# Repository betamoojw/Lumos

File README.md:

# Lumos - Smart Lighting for Better Sleep
There are plenty of smart lighting systems out there that let you change light colors and dim with just your smartphone (or even your voice), but this Open Source lamp called Lumos is a smart lighting system that works to benefit your health.

Lumos mimics the natural light of the sun as it passes overhead each day, generating bright blue light in the morning and warmer amber light in the evening.
Decades of research from Harvard Medical School , NASA , and leading institutions around the world have revealed a great deal of information about how light impacts and regulates our health. They explain that blue light aids in the production of cortisol, which is important to give the human body energy in the morning, and red light aids in the production of sleep-inducing melatonin.
Almost 20% of the world's population is sleep deprived & possibly spends more than 8 hours a day under an unnatural light, which can throw off the body’s internal clock and prevent it from performing at optimum levels.

The Lumos smart lamp aims to change that by pairing with WiFi and uses Machine Learning to adjust the light to match your sleep schedule.

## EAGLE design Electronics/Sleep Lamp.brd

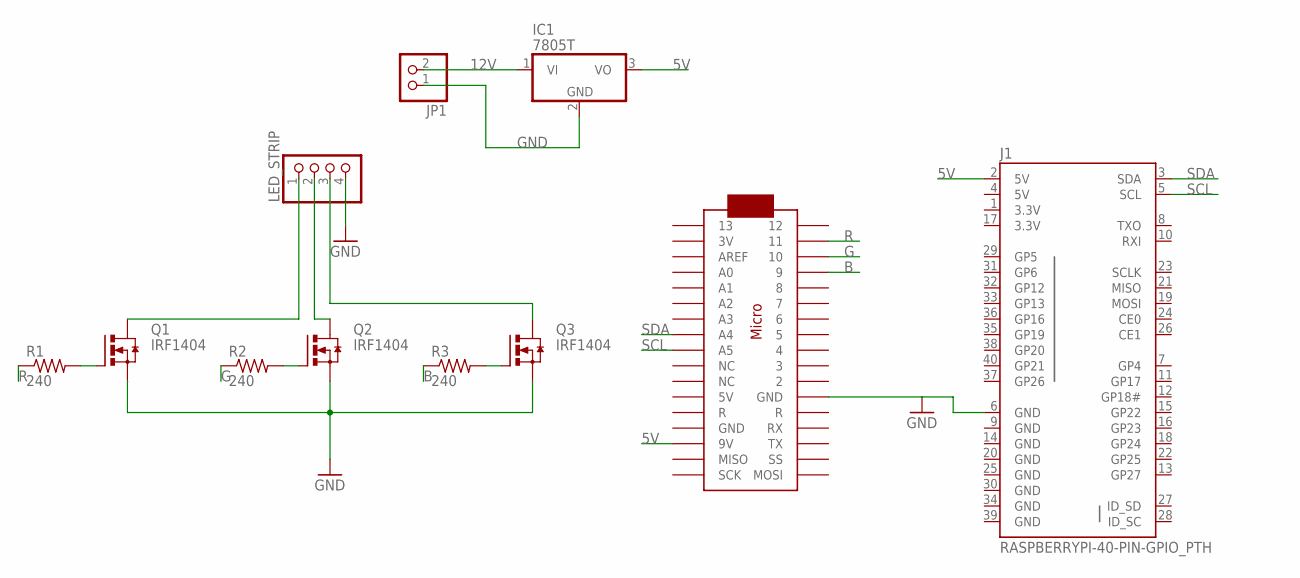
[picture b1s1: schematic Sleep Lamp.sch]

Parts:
IC1: 7805T; TO220H
J1: RASPBERRYPI-40-PIN-GPIO_PTH; 2X20_SHROUDED
JP1: PINHD-1X2; 1X02
LED_STRIP: PINHD-1X4; 1X04
Q1, Q2, Q3: IRF1404; TO220BH
R1, R2, R3: 240; 0204/7
U$1: ARDUINOMICRO

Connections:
3.3V: J1.1 (3.3V), J1.17 (3.3V)
5V: IC1.3 (VO), J1.2 (5V), J1.4 (5V), U$1.P$20 (9V)
12V: IC1.1 (VI), JP1.2
B: R3.1, U$1.P$4 (9)
G: R2.1, U$1.P$3 (10)
GND: IC1.2 (GND), J1.6 (GND), J1.9 (GND), J1.14 (GND), J1.20 (GND), J1.25 (GND), J1.30 (GND), J1.34 (GND), J1.39 (GND), JP1.1, LED_STRIP.4, Q1.S, Q2.S, Q3.S, U$1.P$21 (GND)
unnamed: LED_STRIP.2, Q2.D
unnamed: LED_STRIP.3, Q3.D
unnamed: LED_STRIP.1, Q1.D
unnamed: Q1.G, R1.2
unnamed: Q2.G, R2.2
unnamed: Q3.G, R3.2
R: R1.1, U$1.P$2 (11)
SCL: J1.5 (SCL), U$1.P$26 (A5)
SDA: J1.3 (SDA), U$1.P$27 (A4)

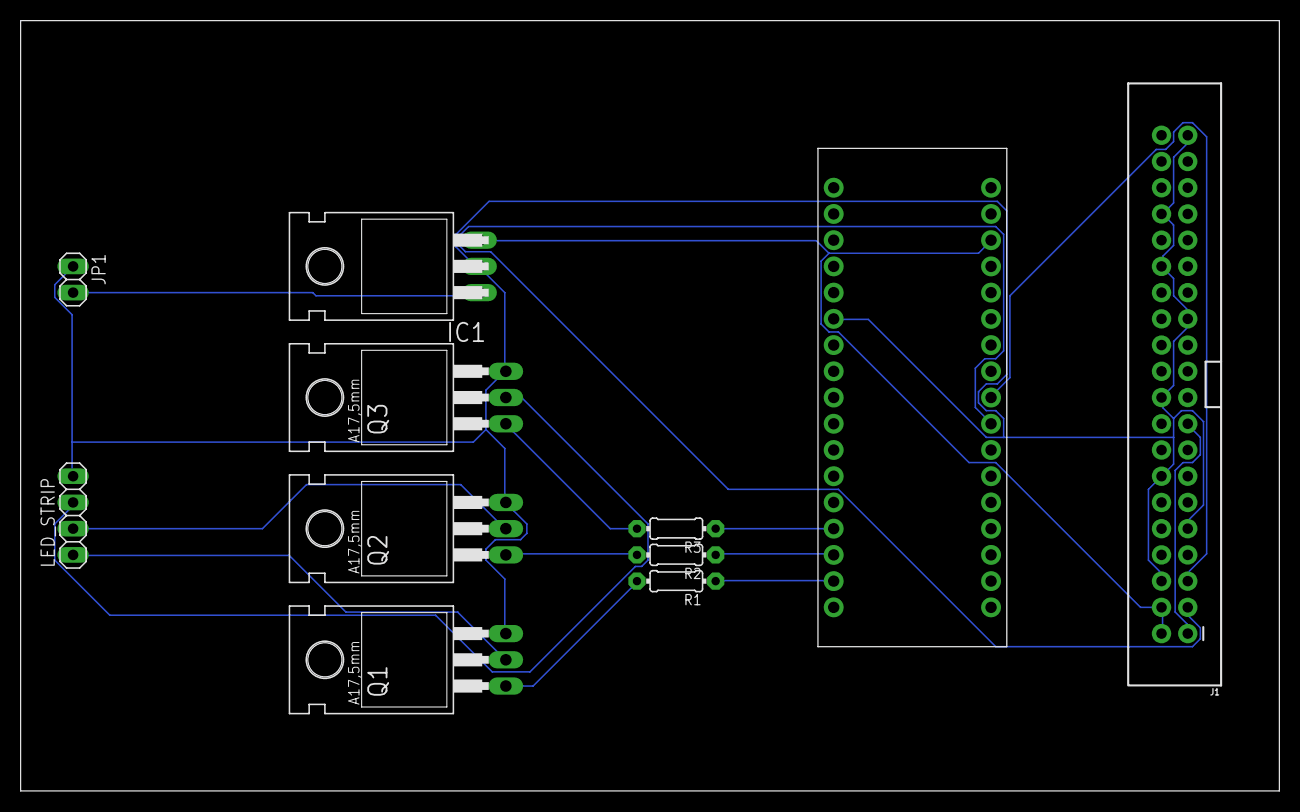
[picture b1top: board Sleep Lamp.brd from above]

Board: 2 copper layers, 121.9 x 74.6 mm, 11 parts (0 on the bottom side), 15 nets.

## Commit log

2016-06-17 :confetti_ball: Added .gitattributes & .gitignore files
2016-06-17 Initial Commit
    Initial Commit
2016-06-19 Average
    Test code to check whether Averaging works
2016-06-22 Average Float
    Each element of average list of a day is in float type
2016-06-22 List of Length of 7 elements
    Creates Lists of Average elements of a day; wherein length of the list
    is 7(7hour sleep cycle)
2016-06-22 List of Sublists of 7 elements
    Creates a List of sublists. Each sublist has length 7. i.e: 7 elements
    per sublist
    Hence List(z) has 26 elements wherein 24 are sublists.
2016-06-22 Sleeping period List
    Creates a list of sublists having 7 elements each from 5pm to
    7am(Sleeping period)
2016-06-23 Average of each 7hour sublist
    Creates a list containing where each element is the average of the 7hour
    sublist respectively
2016-06-23 Order of 7 hour list
    In this change the problem of two or more maximum values turning up in
    the later part of the code can be ignored since the code will choose the
    earliest sleeping period of 7Hours
2016-06-23 Max used 7 hour time period
    Returns index of the maximum used 7 hour time frame.
2016-06-23 Z size & count
    Z size & count
2016-06-23 FAIL
    FAIL
2016-07-06 Edwin added files - main.py and scratch
2016-09-12 Map,lambda,filter update, code reduction
2016-09-13 Index of Maximum slept period of the day
2016-09-13 Time Breakup Table
2016-09-13 Removed File
2016-09-13 Trial code to convert max index to Start Dim hour & Wake up hour
2016-09-13 Added the test.py code to hello.py code
2016-09-13 Indentation
2016-09-25 file change
2017-05-05 Python 3 update
2017-08-03 Mechanical Design
2017-08-05 Eagle Files
    RasPi+Arduino Eagle Files
2017-08-05 LED Calibration
    Arduino Code to test & calibrate colors of the LED Strip.
    TestRGB: Calibrates R,G,B values for indiviual colors.
    CrossFade: Used to test crossfade between the shades of the RGB range.
2017-08-05 Bluetooth Proximity Calibration
2017-08-05 Render & Exploded Design
2017-08-05 Laser Cutting Files
2017-11-06 Schematic & Board View
2017-11-06 LED Calibration

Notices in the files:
parts and their libraries:
SparkFun-Connectors: Licensing: Creative Commons ShareAlike 4.0 International - https://creativecommons.org/licenses/by-sa/4.0
